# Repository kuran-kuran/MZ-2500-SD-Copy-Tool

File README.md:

# SHARP MZ-2500 SD Copy Tool

　MZ-2500のジョイスティックポート1に挿したSD-dongleのSD-CARDとMZ-2500のFD、HDD間でOBT、BTX、BSDファイルを相互にコピーできるツールです。

　Windows等のツールで作成したMZ-2500用の機械語及びBASICプログラムをMZ-2500のFD、HDDにコピー、MZ-2500のFD、HDDのファイルを取り出してWindows等のツールで修正し、MZ-2500のFD、HDDに戻す等が簡単にできます。

## 回路図
　KiCadフォルダ内のSD_dongle.pdfを参照してください。

[回路図](https://github.com/yanataka60/MZ-2500-SD-Copy-Tool/blob/main/Kicad/SD_dongle.pdf)

|番号|品名|数量|備考|
| ------------ | ------------ | ------------ | ------------ |
|J1|D-SUBコネクター9Pメス|1|マルツ 3223DB9RS1S2等|
||J2、J3のいずれか|||
|J2|Micro_SD_Card_Kit|1|秋月電子通商 AE-microSD-LLCNV (注1)|
|J3|MicroSD Card Adapter|1|Arduino等に使われる5V電源に対応したもの(注2)|
|U1|Arduino_Pro_Mini_5V|1|Atmega328版を使用 168版は不可。(注3)|
||ピンソケット(任意)|12Pin×2|Arduino_Pro_Miniを取り外し可能としたい場合に調達します 秋月電子通商 FHU-1x42SGなど|

### 注1)秋月電子通商　AE-microSD-LLCNVのJ1ジャンパはショートしてください。

### 注2)MicroSD Card Adapterを使う場合

J3に取り付けます。

MicroSD Card Adapterについているピンヘッダを除去してハンダ付けするのが一番確実ですが、J2の穴にMicroSD Card Adapterをぴったりと押しつけ、裏から多めにハンダを流し込むことでハンダ付けをする方法もあります。なお、この方法の時にはしっかりハンダ付けが出来たかテスターで導通を確認しておいた方が安心です。

ハンダ付けに自信のない方はJ1の秋月電子通商　AE-microSD-LLCNVをお使いください。AE-microSD-LLCNVならパワーLED、アクセスLEDが付いています。

### 注3)MZ-2500 SD Copy Tool用SD-DongleではArduino Pro MiniのA4、A5ピンは使用しません。

## Arduinoへの書込み
　Arduino IDEを使ってArduinoフォルダSD_dongleフォルダ内SD_dongle.inoを書き込みます。

　SdFatライブラリを使用しているのでArduino IDEメニューのライブラリの管理からライブラリマネージャを立ち上げて「SdFat」をインストールしてください。

　「SdFat」で検索すれば見つかります。「SdFat」と「SdFat - Adafruit Fork」が見つかりますが「SdFat」のほうを使っています。

## MZ-2500用Copy Toolプログラム
　MZ-2500のFD、HDD、FDDエミュレータ用FDイメージにOBTファイルを転送する手段がある方はSD_TRANSフォルダ内のSD_TRANS.binを転送してください。

　転送する手段の無い方はBASIC-S25又はBASIC-M25からモニタMコマンドでSD_LOADERフォルダ内のSD_LOADER.binの内容を入力します。

　入力間違いが無いことを確認し、SコマンドでSD_LOADER.bin等の名前を付けてセーブしてください。

　　*S A000 A16F A000:SD_LOADER.bin

　次にSD_TRANSフォルダ内のSD_TRANS.binをSD-CARDにコピーし、次のコマンドを実行します。

### (BASIC-M25)

　clear &HA000

　bload "SD_LOADER.bin"

　FD、HDDのカレントディレクトリをSD_TRANS.bin転送先ディレクトリに変更

　call &HA000

### (BASIC-S25)

　limit &HA000

　load "SD_LOADER.bin"

　FD、HDDのカレントディレクトリをSD_TRANS.bin転送先ディレクトリに変更

　call &HA000

　問題が無ければ「OK」と表示されて終了し、SD_TRANS.binがFD、HDDのカレントディレクトリに転送されているはずです。

## SD-CARD
　出来れば8GB以下のSDカードを用意してください。

　ArduinoのSdFatライブラリは、SD規格(最大2GB)、SDHC規格(2GB～32GB)に対応していますが、SDXC規格(32GB～2TB)には対応していません。

　また、SDHC規格のSDカードであっても32GB、16GBは相性により動作しないものがあるようです。

　FAT16又はFAT32が認識できます。NTFSは認識できません。

## 操作方法
　clear又はlimitで機械語領域を確保してからbload又はloadコマンドでSD_TRANS.binをロードします。

　必要があればFD又はHDDのカレントディレクトリを変更しておきます。

　SD-Dongleをジョイスティックポート1に挿します。

　call &HA000でCopy Toolを実行します。

　SD-CARDのファイル名は拡張子も含めて32文字まで、ただし漢字、半角カタカナ、及び一部の記号はArduinoが認識しないので使えません。パソコンでファイル名を付けるときはアルファベット、数字および空白でファイル名をつけてください。

　また、SD-CARDからFD、HDDにコピーされたファイルのファイル名は先頭16文字までとなります。

　Copy Toolが起動したらまず処理の選択をします。

### 1 SD -> FD
　SD-CARDのファイルをFD、HDDにコピーします。

　次にSD-CARDのファイル名を指定します。

　大文字、小文字は区別されるので大文字、小文字も正確に入力してください。

　FD、HDDにはSD-CARDのファイル名のままコピーされますが、16文字を超えた分は切り捨てられます。

　ファイルモードを指定します。SD-CARDのファイルにはファイルモード等の情報が含まれていないため指定する必要があります。

　実際のファイルモードと指定したファイルモードが間違っていてもコピーは正常終了しますが、MZ-2500のBASICからは期待した動作が出来なくなりますので削除してください。

#### 1 OBT
　SD-CARDのファイルには先頭アドレス、実行アドレスの情報が含まれていないため指定する必要があります。

#### 2 BXT
　ファイルモードを指定するだけでコピーが始まります。

#### 3 BSD
　ファイルモードを指定するだけでコピーが始まります。

　BSDファイルとはテキストファイルであり、Windows等のテキストエディタでBASICのプログラムとして入力することも可能です。

　ただし、改行コードは0Dhのみ(Windowsのテキストの改行コードは通常0Dh,0Ah)、漢字コードはSHIFTJISで作成してください。

## 注意!!
　SD-CARDからコピーされるファイル名のファイルがコピー先のFD、HDD上に既にある場合、エラー終了します。

　この「already exist error」で中止されたことをArduinoは認識できないため転送処理が中途半端なまま待機状態となっており、次にCopy Toolが起動されても正常に処理できません。

## 　SD-Dongleを挿し直すことで正常に処理できるよう復旧するので、もう一度Copy Toolを起動する前に必ずSD-Dongleを挿し直してください。

　FD、HDD上に既にあるファイルもCopy Tool起動前には削除してください。

### 2 FD -> SD
　FD、HDDのファイルをSD-CARDにコピーします。

　FD、HDDのファイル名を指定します。

　SD-CARDにコピーされるファイルのファイル名にはFD、HDD上のファイル情報に基づき、拡張子及び先頭アドレス、実行アドレスが付加されます。

　　[OBTファイル] test.OBJ -> test.OBJ_A000_A000.OBT

　　[BTXファイル] test.m25 -> test.m25.BTX

　　[BSDファイル] test     -> test.BSD

### 3 SD DIR
　SD-CARDのルートディレクトリにあるファイル一覧からファイルを選択することでSD-CARDのファイルをFD、HDDにコピーできます。

　「SD-CARD Search Name?」と聞いてくるので文字列を何も指定せずにENTERキーのみとするとSD-CARDルートディレクトリにあるファイルの一覧を表示します。

　文字列を指定するとSD-CARDルートディレクトリにあるその文字列から始まるファイルの一覧を表示します。

　10件表示したところで指示待ちになるので打ち切るならESCキー、Bキーで前の10件に戻ります。それ以外のキーで次の10件を表示します。

　行頭に0から9の数字を付加して表示してあるのでコピーしたいファイルの頭についている数字を入力するとコピー処理に移行します。

　検索する文字列は大文字、小文字の区別はありません。大文字、小文字のどちらで入力しても大丈夫です。

　表示される順番は、登録順となりファイル名アルファベッド順などのソートした順で表示することはできません。

## 追記
2024.11.30　Arduinoプログラムに安定性の向上を追加

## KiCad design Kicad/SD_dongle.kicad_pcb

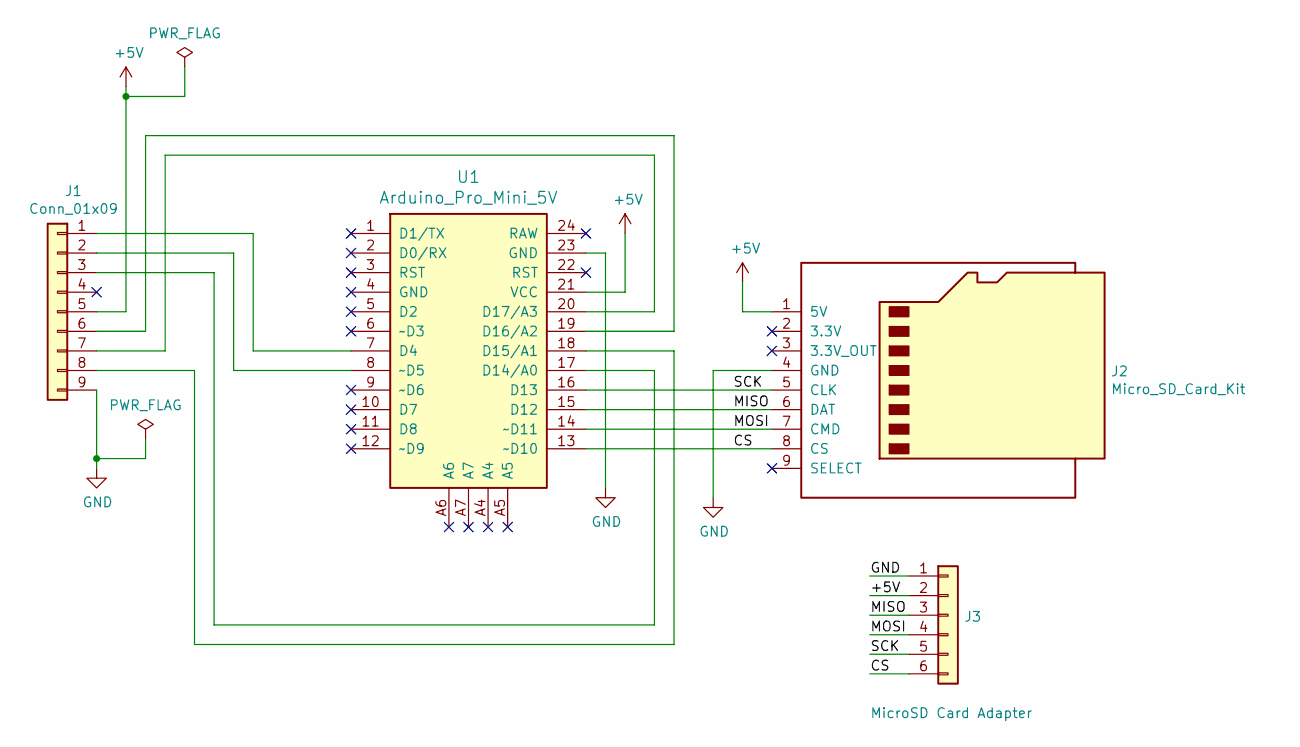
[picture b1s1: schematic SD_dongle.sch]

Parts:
J1: Conn_01x09; DSUB-9_Female_Horizontal_P2.77x2.84mm_EdgePinOffset7.70mm_H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
J2: Micro_SD_Card_Kit; AE-microSD-LLCNV
J3: MicroSD Card Adapter; PinSocket_1x06_P2.54mm_Vertical
U1: Arduino_Pro_Mini_5V; Arduino_Pro_Mini

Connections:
+5V: J1.5, J2.1 (5V), J3.2, U1.21 (VCC)
/CS: J2.8 (CS), J3.6, U1.13 (~~D10)
/MISO: J2.6 (DAT), J3.3, U1.15 (D12)
/MOSI: J2.7 (CMD), J3.4, U1.14 (~~D11)
/SCK: J2.5 (CLK), J3.5, U1.16 (D13)
GND: J1.9, J2.4 (GND), J3.1, U1.23 (GND)
unnamed: J1.1, U1.7 (D4)
unnamed: J1.2, U1.8 (~~D5)
unnamed: J1.3, U1.17 (D14/A0)
unnamed: J1.6, U1.19 (D16/A2)
unnamed: J1.7, U1.20 (D17/A3)
unnamed: J1.8, U1.18 (D15/A1)

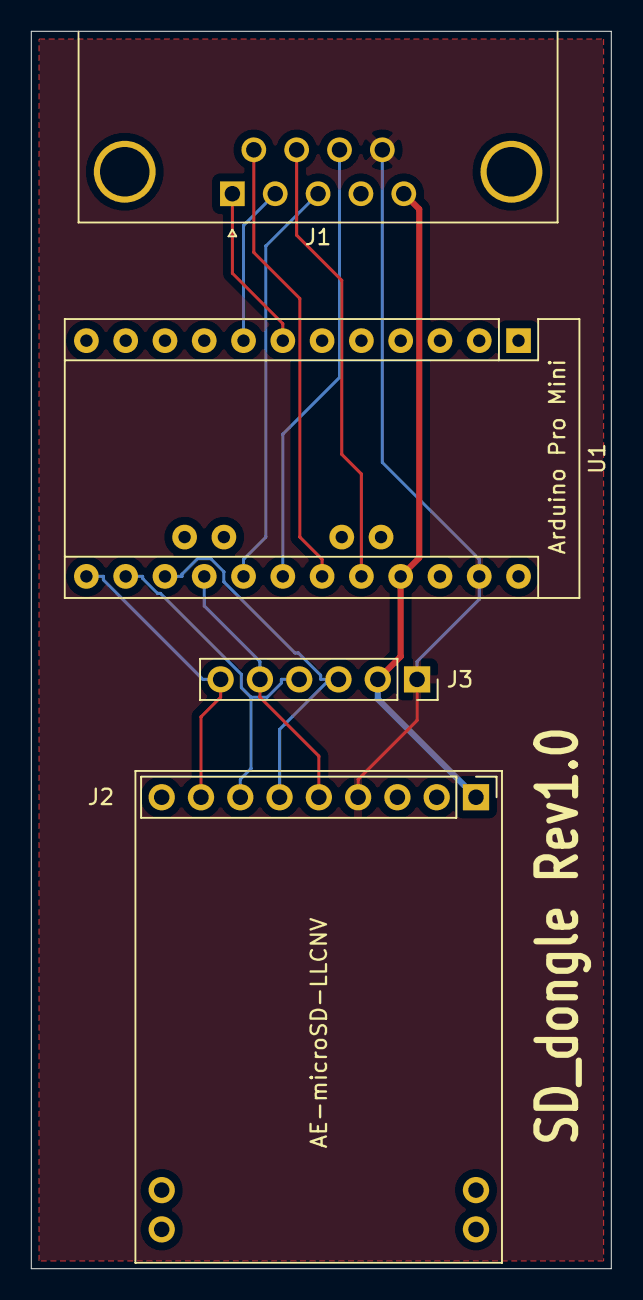
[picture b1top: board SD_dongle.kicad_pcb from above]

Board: 2 copper layers, 37.5 x 80.0 mm, 4 parts (0 on the bottom side), 12 nets.

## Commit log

2024-12-03 SD_TOOL作成開始
2024-12-05 SD_BENCH追加
2024-12-05 SDBENCHがファイル読み込みできるようになった
2024-12-06 SD_BOOT追加
2024-12-06 起動テスト中
2025-02-13 RaspberryPI Picoでビルドできるようにした
2025-04-06 MZ-2000用ベンチマーク作成
2025-04-15 Pico2に転送してSDカードの初期化は成功している。転送は途中でフリーズ。
